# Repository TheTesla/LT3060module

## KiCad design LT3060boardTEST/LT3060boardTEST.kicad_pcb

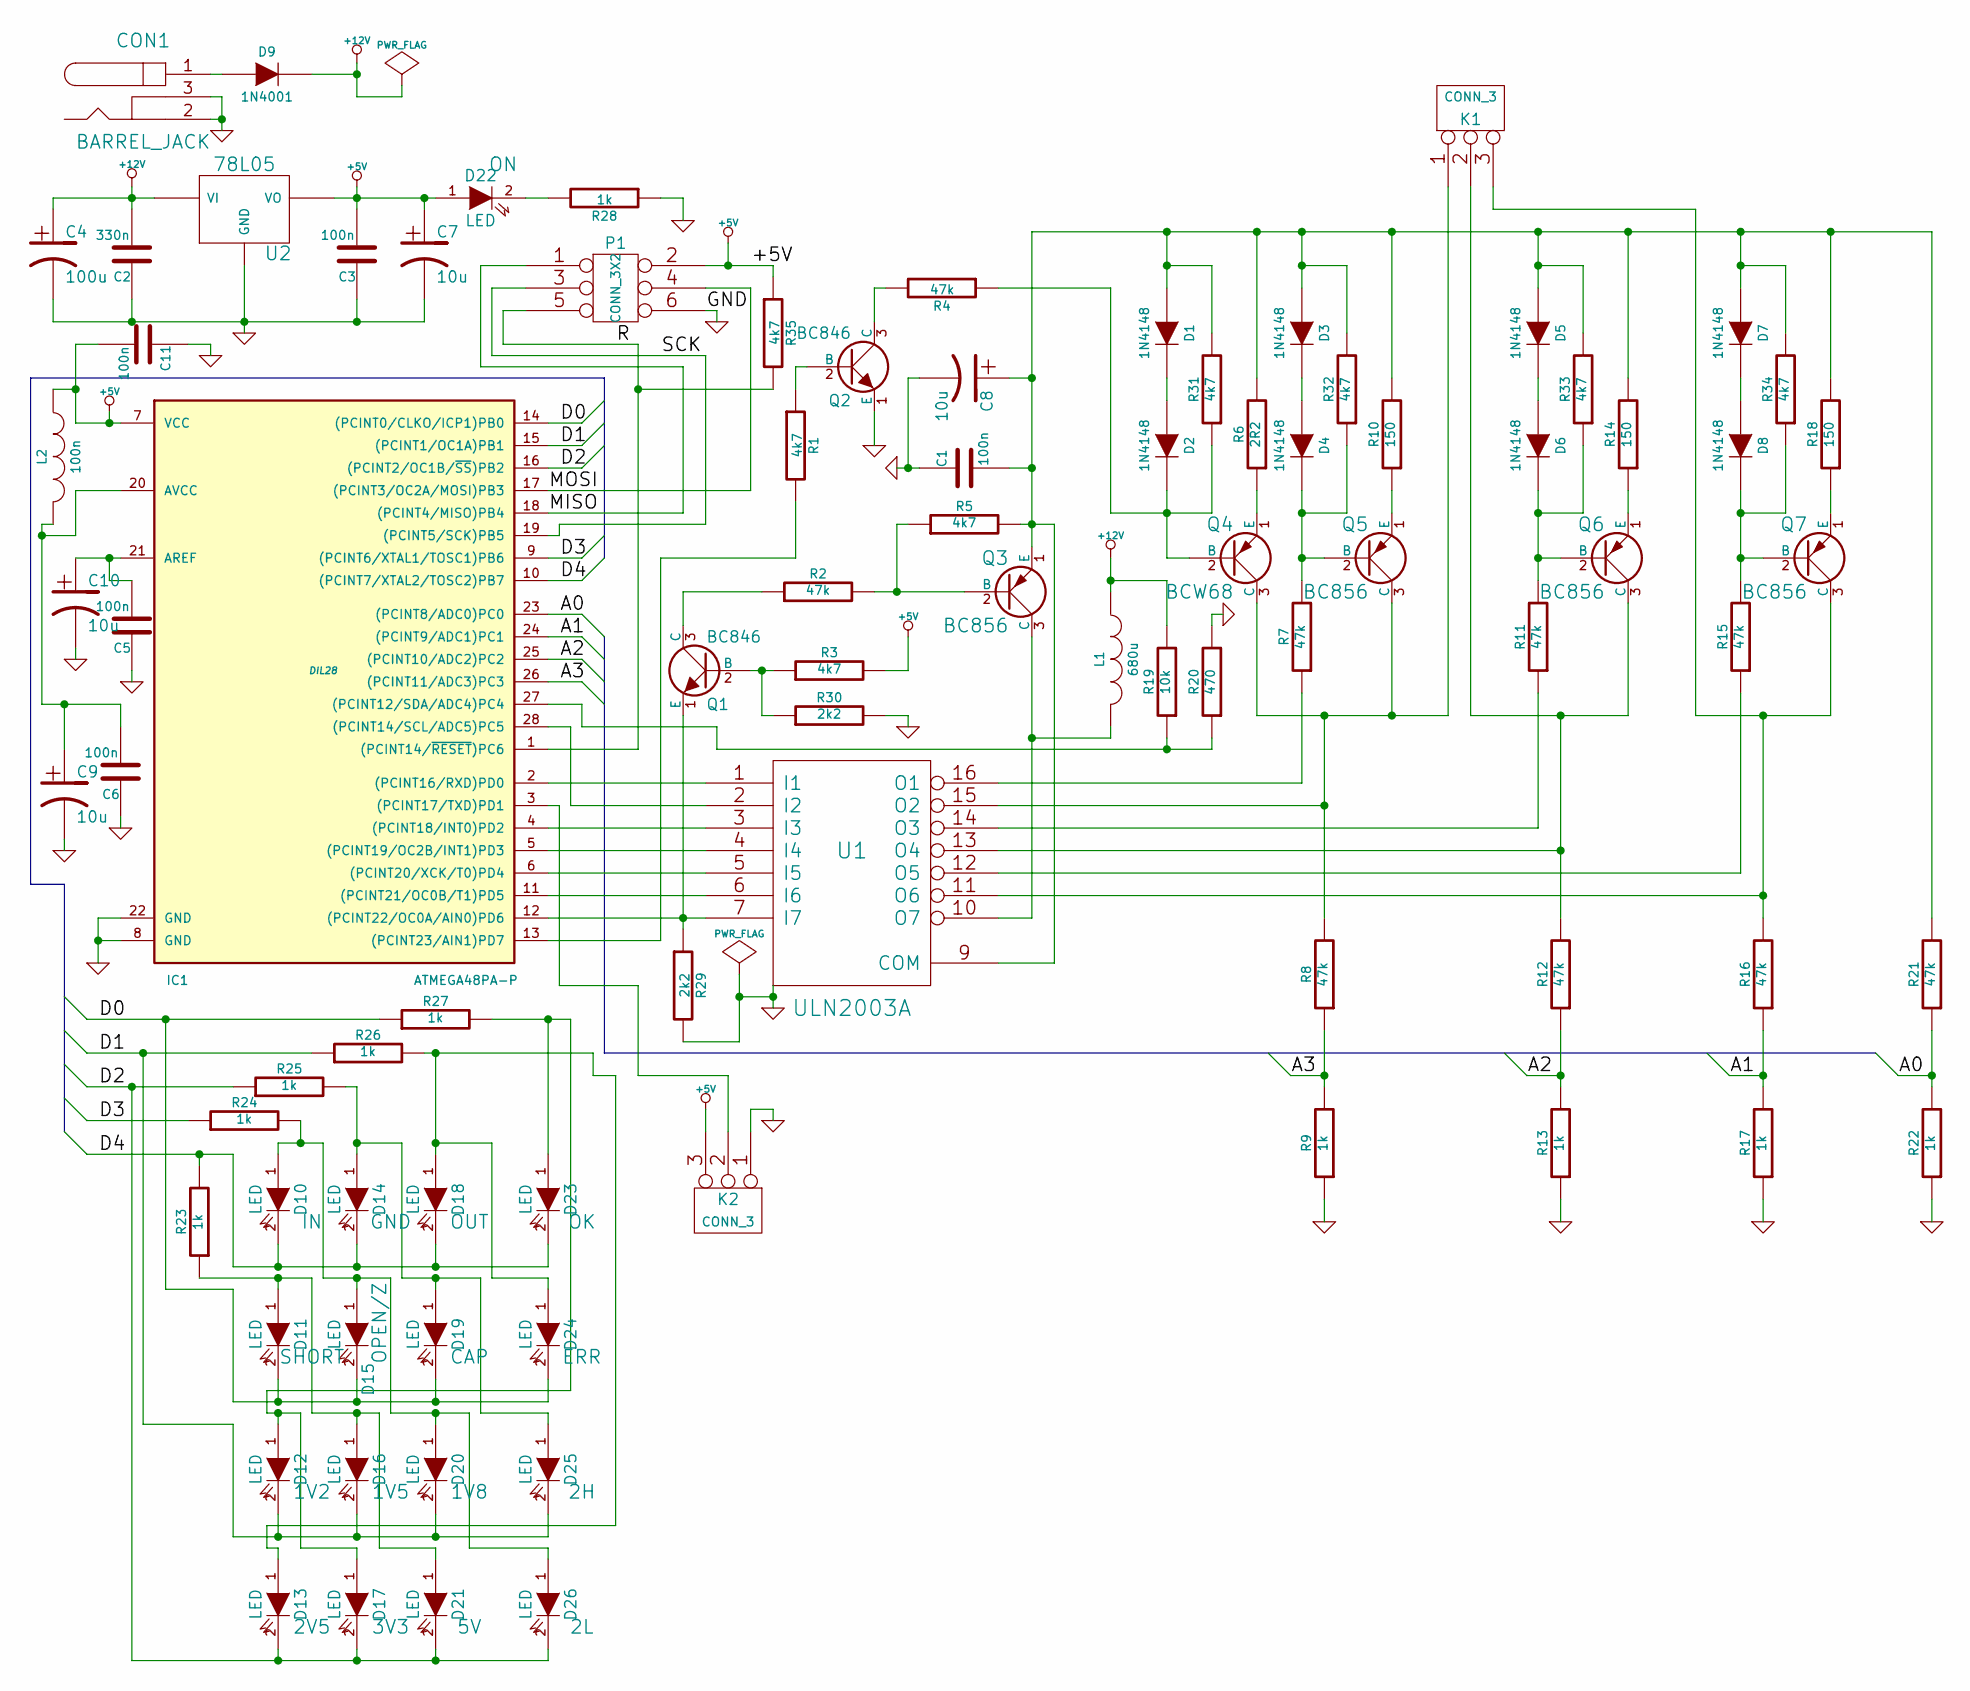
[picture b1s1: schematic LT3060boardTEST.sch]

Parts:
C1: 100n; Voltage 63
C2: 330n
C3, C5, C6, C11: 100n
C4: 100u
C7, C9, C10: 10u
C8: 10u; Voltage 63
CON1: BARREL_JACK
D1, D2, D3, D4, D5, D6, D7, D8: 1N4148
D9: 1N4001
D10, D11, D12, D13, D14, D15, D16, D17, D18, D19, D20, D21, D22, D23, D24, D25, D26: LED
IC1: ATMEGA48PA-P; DIL28
K1, K2: CONN_3
L1: 680u
L2: 100n
P1: CONN_3X2
Q1, Q2: BC846
Q3, Q5, Q6, Q7: BC856
Q4: BCW68
R1, R3, R5, R31, R32, R33, R34, R35: 4k7
R2, R4, R7, R8, R11, R12, R15, R16, R21: 47k
R6: 2R2
R9, R13, R17, R22, R23, R24, R25, R26, R27, R28: 1k
R10, R14, R18: 150
R19: 10k
R20: 470
R29, R30: 2k2
U1: ULN2003A
U2: 78L05

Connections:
+5V: C3.2, C7.1, C11.2, D22.1 (A), IC1.7 (VCC), K2.3, L2.1, P1.2, R3.2, R35.1, U2.VO
+12V: C2.2, C4.1, D9.2 (K), L1.1, R19.2, U2.VI
/A0: IC1.23 ((PCINT8/ADC0)PC0), R21.1, R22.2
/A1: IC1.24 ((PCINT9/ADC1)PC1), R16.1, R17.2
/A2: IC1.25 ((PCINT10/ADC2)PC2), R12.1, R13.2
/A3: IC1.26 ((PCINT11/ADC3)PC3), R8.1, R9.2
/D0: D11.2 (K), D15.2 (K), D19.2 (K), D24.2 (K), IC1.14 ((PCINT0/CLKO/ICP1)PB0), R27.1
/D1: D12.2 (K), D16.2 (K), D20.2 (K), D25.2 (K), IC1.15 ((PCINT1/OC1A)PB1), R26.1
/D2: D13.2 (K), D17.2 (K), D21.2 (K), D26.2 (K), IC1.16 ((PCINT2/OC1B/~SS~)PB2), R25.1
/D3: IC1.9 ((PCINT6/XTAL1/TOSC1)PB6), R24.1
/D4: D10.2 (K), D14.2 (K), D18.2 (K), D23.2 (K), IC1.10 ((PCINT7/XTAL2/TOSC2)PB7), R23.2
/MISO: IC1.18 ((PCINT4/MISO)PB4), P1.1
/MOSI: IC1.17 ((PCINT3/OC2A/MOSI)PB3), P1.4
/R: IC1.1 ((PCINT14/~RESET~)PC6), P1.5, R35.2
/SCK: IC1.19 ((PCINT5/SCK)PB5), P1.3
GND: C1.1, C2.1, C3.1, C4.2, C5.1, C6.1, C7.2, C8.2, C9.2, C10.2, C11.1, CON1.2, CON1.3, IC1.8 (GND), IC1.22 (GND), K2.1, P1.6, Q2.1 (E), R9.1, R13.1, R17.1, R20.2, R22.1, R28.1, R29.2, R30.2, U1.8 (GND), U2.GND
unnamed: D11.1 (A), D16.1 (A), D21.1 (A), R23.1
unnamed: D13.1 (A), D18.1 (A), D24.1 (A), R26.2
unnamed: D14.1 (A), D19.1 (A), D25.1 (A), R25.2
unnamed: D10.1 (A), D15.1 (A), D20.1 (A), D26.1 (A), R24.2
unnamed: IC1.27 ((PCINT12/SDA/ADC4)PC4), R19.1, R20.1
unnamed: D12.1 (A), D17.1 (A), D23.1 (A), R27.2
unnamed: IC1.3 ((PCINT17/TXD)PD1), K2.2 (PM)
unnamed: C5.2, C10.1, IC1.21 (AREF)
unnamed: IC1.28 ((PCINT14/SCL/ADC5)PC5), U1.2 (I2)
unnamed: C6.2, C9.1, IC1.20 (AVCC), L2.2
unnamed: CON1.1, D9.1 (A)
unnamed: D22.2 (K), R28.2
unnamed: IC1.2 ((PCINT16/RXD)PD0), U1.1 (I1)
unnamed: IC1.13 ((PCINT23/AIN1)PD7), R1.2
unnamed: Q3.2 (B), R2.2, R5.1
unnamed: Q1.3 (C), R2.1
unnamed: D2.2 (K), Q4.2 (B), R4.1, R31.1
unnamed: IC1.4 ((PCINT18/INT0)PD2), U1.3 (I3)
unnamed: IC1.5 ((PCINT19/OC2B/INT1)PD3), U1.4 (I4)
unnamed: IC1.6 ((PCINT20/XCK/T0)PD4), U1.5 (I5)
unnamed: IC1.11 ((PCINT21/OC0B/T1)PD5), U1.6 (I6)
unnamed: Q1.2 (B), R3.1, R30.1
unnamed: D5.2 (K), D6.1 (A)
unnamed: D7.2 (K), D8.1 (A)
unnamed: Q4.1 (E), R6.1
unnamed: D1.2 (K), D2.1 (A)
unnamed: Q2.2 (B), R1.1
unnamed: Q2.3 (C), R4.2
unnamed: D8.2 (K), Q7.2 (B), R15.2, R34.1
unnamed: R7.1, U1.16 (O1)
unnamed: D6.2 (K), Q6.2 (B), R11.2, R33.1
unnamed: R11.1, U1.14 (O3)
unnamed: R15.1, U1.12 (O5)
unnamed: Q5.1 (E), R10.1
unnamed: Q6.1 (E), R14.1
unnamed: C1.2, C8.1, D1.1 (A), D3.1 (A), D5.1 (A), D7.1 (A), Q3.1 (E), R5.2, R6.2, R10.2, R14.2, R18.2, R21.2, R31.2, R32.2, R33.2, R34.2, U1.9 (COM)
unnamed: Q7.1 (E), R18.1
unnamed: D3.2 (K), D4.1 (A)
unnamed: K1.3, Q7.3 (C), R16.2, U1.11 (O6)
unnamed: K1.2 (PM), Q6.3 (C), R12.2, U1.13 (O4)
unnamed: K1.1, Q4.3 (C), Q5.3 (C), R8.2, U1.15 (O2)
unnamed: L1.2, Q3.3 (C), U1.10 (O7)
unnamed: IC1.12 ((PCINT22/OC0A/AIN0)PD6), Q1.1 (E), R29.1, U1.7 (I7)
unnamed: D4.2 (K), Q5.2 (B), R7.2, R32.1

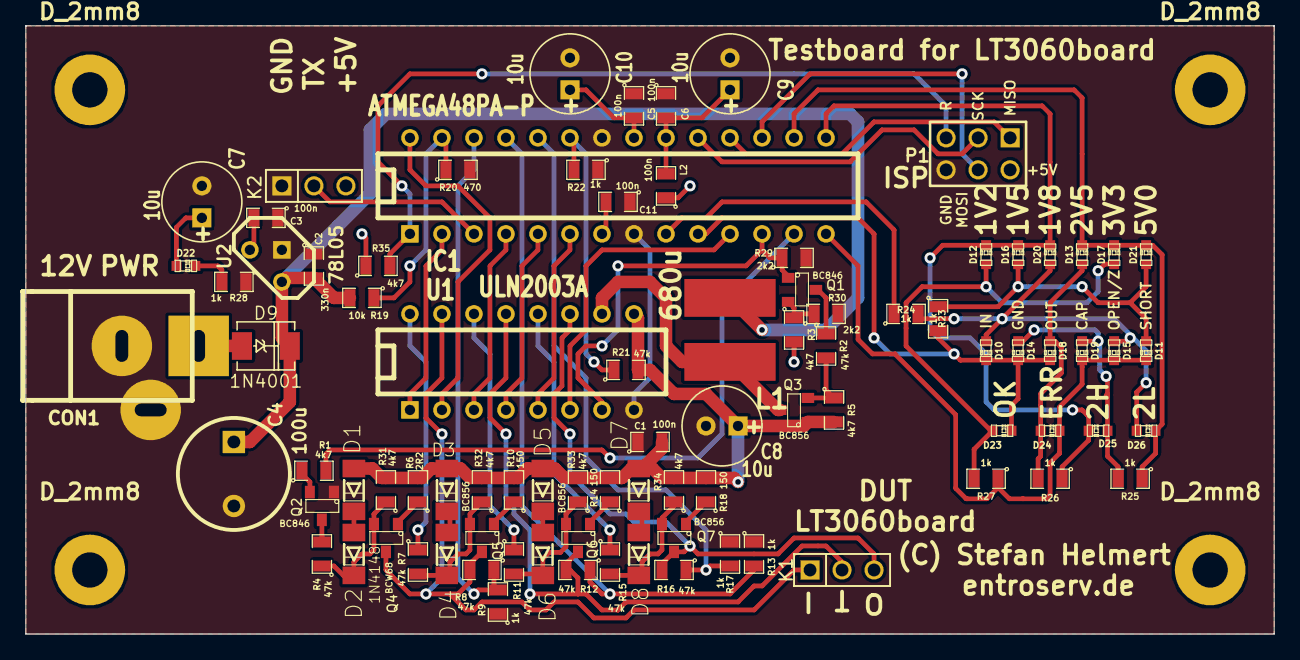
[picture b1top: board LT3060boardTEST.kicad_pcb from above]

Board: 2 copper layers, 99.1 x 48.3 mm, 92 parts (0 on the bottom side), 60 nets.

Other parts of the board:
D_2mm8, D_2mm8#2, D_2mm8#3, D_2mm8#4: VAL**; SOLEIL-D_2mm8

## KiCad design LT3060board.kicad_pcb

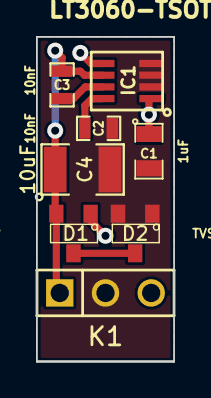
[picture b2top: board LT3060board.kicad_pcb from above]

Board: 2 copper layers, 7.6 x 18.0 mm, 8 parts (0 on the bottom side), 6 nets.

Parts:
C1: 1uF; SM0805
C2, C3: 10nF; SM0603_Capa
C4: 10uF; SM1210
D1, D2: TVSCOMA; SOT23
IC1: LT3060-TSOT; tsot23-8
K1: CONN_3; PIN_ARRAY_3X1

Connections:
/Vin: C1.1, D1.1, IC1.1, IC1.5, K1.3
/Vout: C3.1, C4.1, D1.2, IC1.6, K1.1
GND: C1.2, C2.2, C4.2, D2.1, D2.2, IC1.2, IC1.3, IC1.4, K1.2
unnamed: C2.1, IC1.8
unnamed: C3.2, IC1.7
unnamed: D1.3, D2.3

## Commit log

2014-08-03 Schematic, layout ready
2014-08-03 more nice
2014-08-27 Version with 3 TVS-diodes for protection.
2014-08-27 little changes in silkscreen
2014-08-27 just forgot to run ./rename.sh
2014-08-27 edited edge cuts
2014-08-28 LT3060 protected by more compact TVS-diodes
2014-09-18 Testboard ready - first version of produced Testboard
2015-07-05 test useable (z-diode test, cap test, voltage test) - no over current test
2015-07-15 check test board step up regulator, priority of test board self test errors; LT3060boards for other voltages (silk screen); test instruction manual
